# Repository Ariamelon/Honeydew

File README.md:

# Honeydew
~60% 63-key QMK-compatible unified split ergonomic keyboard.

## Disclaimer
This keyboard is licensed under CERN-OHL-S-2.0 and runs [QMK Firmware](https://qmk.fm/). The layout is based on the [Cantaloupe](https://github.com/Ariamelon/Cantaloupe) layout, but with each half rotated 15 degrees inwards.

## Key Features
* Ergonomic unsplit 60-key vertically staggered layout with thumb cluster, pinky stagger and arrow keys, plus 3 keys in the middle.
* Each half is rotated 15 degrees inwards.
* On-board Raspberry Pi RP2040 processor.
* Uses shift registers for the columns.
* SWD header for debugging purposes.
* USB-C input with full ESD protection and up to 15W of power depending on source capability.
* MX switch support with kailh hot-swap sockets.
* 40mm cirque trackpad support in the middle, alternately supports a 34mm trackball instead of the trackpad.
* Per-key RGB backlight, illuminated center ring and ARGB header for adding more.
* Rotary encoder ring around the trackball or trackpad.
* 1.5" 128x128 SSD1351 RGB QP OLED support, either bare OLED panel or using the Waveshare breakout board.
* Gasket-mount case held together with magnets.

## Changelog
* 22/10/2024: License updated to CERN-OHL-S-2.0.
* 11/06/2023: Updated BOM. Added new tentative plate file. Updated 3D files.
* 20/05/2023: Added scroll wheel rotary encoder and mouse switch for thumb scroll wheel, replacing bottom 2u key.
* 19/05/2023: Improved switch footprints. Changed 3v3 regulator to XC6206P332MR.
* 15/05/2023: Finished routing RGB LEDs.
* 05/05/2023: Changed PMOS switch to TPS2595, set to ~3A current limit. Got rid of RGB current measurement. Added enable jumper for 13V OLED PSU (only jump when in use to reduce noise when not in use). Still not done with RGB LED routing.
* 25/04/2023: Added current and voltage measurement for VBUS in and current measurement for the RGB output. Added PMOS power switch to fully turn off RGB LEDs when not in use. Rerouted the PCB. Moved OLED ribbon cable cutout and expanded it length-wise. Changed position of various components for better routing. Changed bulk capacitance of RGB LEDs to 5 x 22u capacitors. Changed the four N mosfets to two much smaller dual N mosfets. Still need to do RGB routing!
* 17/04/2023: Large update. Changed position of thumb buttons and added another button. Revamped shape of PCB again. Changed PER60 to PER56. Added 30-pin FFC receptacle for direct OLED panel mounting to the PCB (lower profile). Now using 595 shift registers for columns. Increased number of LEDs in central LED ring. Changed current limiting device to TPS2595. Connected current limiting ICs to MCU, allowing for software monitoring of current levels and changing of allowed current. Removed individual RGB capacitors and added bulk capacitance.
* 10/04/2023: Shrunk size of PCB. Added plate DXF and gerbers. Removed split comms ports and ideal diode.
* 08/04/2023: Large update. Removed single-push reset circuit, added side buttons next to the USB ports. Added pi filter to VBUS and split comms ports for more voltage filtering. Completely revamped shape of PCB for more space efficiency. Pushed each side further out and OLED further down. Added TUSB320 CC logic controller and TPS2557 current limit switch to allow the board to safely draw up to 15W (5V 3A) of power. Added mounting holes on PCB. Removed ferrite between USB shield and ground. Replaced back to back P-mosfets with ideal diode setup. Removed QMK logo (sorry). Cleaned up schematic somewhat. Added large caps to output of TPS2557. Updated STEP file and file data. Added back ground plane. Fixed rotation of production files.
* 03/04/2023: Changed level shifter to cheaper model. Slightly changed USB-C footprint. Added single-push reset circuit and removed DIP switch. Updated readme and STEP file. Moved position of USB-C ports further out.
* 02/04/2023: Changed angle of each unsplit half to 15 degrees inwards instead of 20 degrees with corresponding change to PCB and plate shape. Re-did 5V routing on the board. Added ARGB header to attach external RGB strips. Removed reverse voltage/current schottky and added back to back P-mosfets to provide the same function. Added ferrite bead to VBUS for more voltage filtering. Changed ESD protection chip to TPD4E05U06DQAR. Added USB-C expansion headers for expansion boards using split comms with the same protections as the primary USB-C input port. Added M3 earth pad for connection to a metal case. Added solder jumper to select OLED voltage as it should work fine when powered by 5V, but the option to power from 3V3 is there if required. Case to follow..
* 31/03/2023: Connected DR (data-ready) pin of TM040040 to Motion pin of PMW3360 as they serve the same function. Connected reset pins to hardware reset button instead of MCU. Added locating features to CNC case, increased wall thickness by 1mm for better magnet support (4mm now instead of 3mm) and increased size of gaskets. Redesigned trackpad mount and rotary encoder knob to allow for the illuminated ring to show up better. Added powered by QMK logo to board.
* 24/04/2023: Added level shifter to the RGB signal, just in case.
* 14/03/2023: Fixed top and bottom case STEP files. Minor fix to silk.
* 13/03/2023: V2.0 initial update. Moved switch footprint center back to normal position. Swapped capacitor and resistor at USB-C connector for ferrite bead. Moved positions of USB VBUS protection. 
* 11/03/2023: Added PH2.0 header for OLED. Changed plate to accommodate headers. Better render.
* 10/03/2023: Fixed OLED description in readme. Changed center of switches for JLC assembly.
* 09/03/2023: Shifted MCU up to reduce length of USB traces. Added holes for JLC assembly. Attempted to render a better quality image.
* 08/03/2023: Added 3D render of case, case STEP files and plate DXF and gerbers.
* 07/03/2023: Rewording of readme. Added files for JLC PCBA. Changed USB C connector and moved it away from board.
* 06/03/2023: Minor repositioning of parts.
* 05/03/2023: Added mounting holes for trackpad/trackball mount. Added CC BY 4.0 license.
* 04/03/2023: Massive mistake corrections and clarifications. Changed 22R USB resistors to 27R. Readded missing pullup for RUN pin. Changed notation of power and ground rails to the standard. Connected RGB LEDs to 5V instead of 3V3. Added keycap model to render. Changed board showcase files from SVG to PDF. Fixed error in MCU sheet. Changed flash symbol to the one used in Kicad 7.
* 03/03/2023: Initial public upload of V1.0.

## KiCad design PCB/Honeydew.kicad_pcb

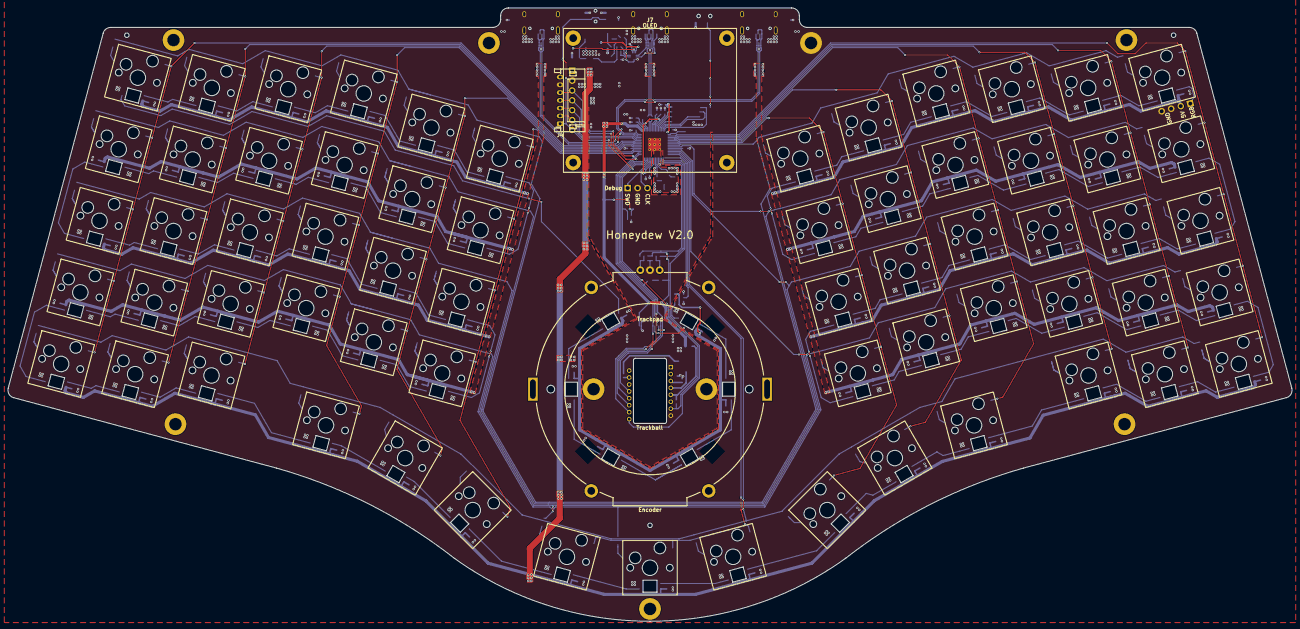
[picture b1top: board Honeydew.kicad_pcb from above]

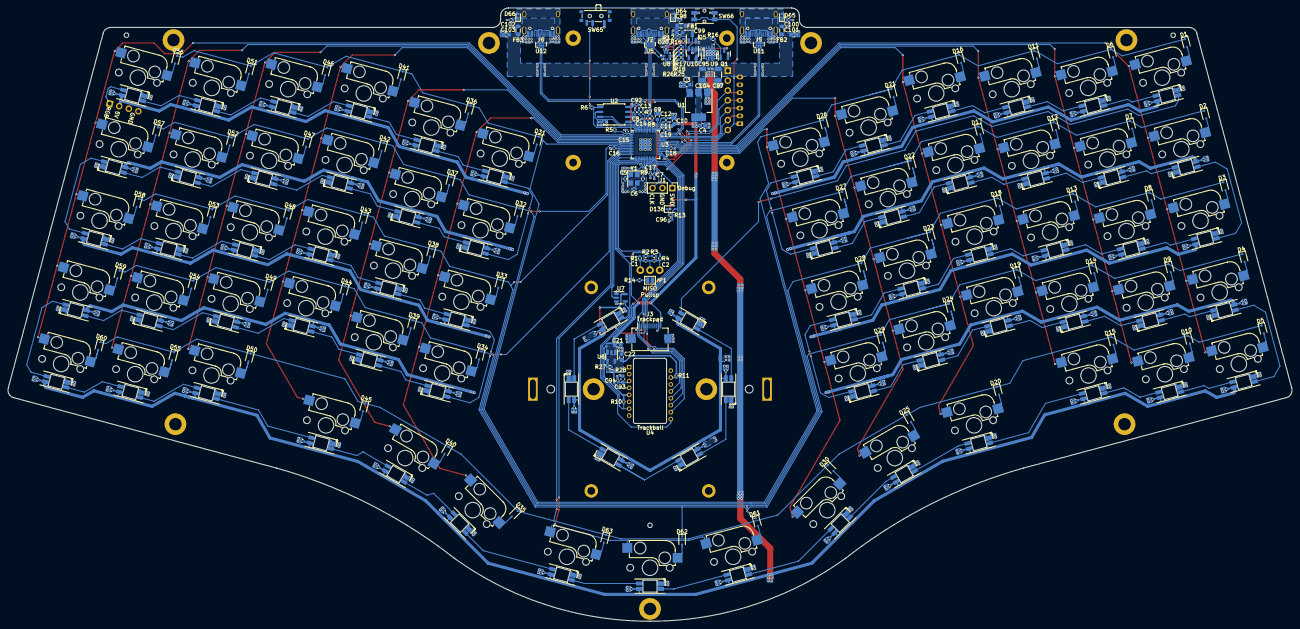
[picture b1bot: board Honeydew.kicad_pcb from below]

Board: 2 copper layers, 330.1 x 157.7 mm, 366 parts (356 on the bottom side), 206 nets.

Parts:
A1: Ariamelon Logo; Ariamelon_Logo_x3_CU
C1, C2, C98, C100, C102: 10n; C_0402_1005Metric
C3, C4, C93: 4u7; C_0603_1608Metric
C5, C6: 22p; C_0402_1005Metric
C7, C8, C11, C12, C13, C14, C15, C16, C17, C18, C19, C20, C23, C24, C25, C26, C27, C28, C29, C30, C31, C32, C33, C34, C35, C36, C37, C38, C39, C40, C41, C42, C43, C44, C45, C46, C47, C48, C49, C50, C51, C52, C53, C54, C55, C56, C57, C58, C59, C60, C61, C62, C63, C64, C65, C66, C67, C68, C69, C70, C71, C72, C73, C74, C75, C76, C77, C78, C79, C80, C81, C82, C83, C84, C85, C86, C87, C88, C89, C90, C91, C92, C94, C95, C96: 100n; C_0402_1005Metric
C9, C10, C21, C22, C99, C101, C103: 1u; C_0603_1608Metric
C97, C104: 47u; C_1206_3216Metric
D1, D2, D3, D4, D5, D6, D7, D8, D9, D10, D11, D12, D13, D14, D15, D16, D17, D18, D19, D20, D21, D22, D23, D24, D25, D26, D27, D28, D29, D30, D31, D32, D33, D34, D35, D36, D37, D38, D39, D40, D41, D42, D43, D44, D45, D46, D47, D48, D49, D50, D51, D52, D53, D54, D55, D56, D57, D58, D59, D60, D61, D62, D63, D136: 1N4148; D_SOD-323
D64, D65, D66: 5V; D_SOD-523
D67, D68, D69, D70, D71, D72, D73, D74, D75, D76, D77, D78, D79, D80, D81, D82, D83, D84, D85, D86, D87, D88, D89, D90, D91, D92, D93, D94, D95, D96, D97, D98, D99, D100, D101, D102, D103, D104, D105, D106, D107, D108, D109, D110, D111, D112, D113, D114, D115, D116, D117, D118, D119, D120, D121, D122, D123, D124, D125, D126, D127, D128, D129, D130, D131, D132, D133, D134, D135: SK6812MINI-E; YS-SK6812MINI-E
FB1, FB2, FB3: 60R@100MHz; L_0805_2012Metric
H1, H2, H3: Tooling Hole; JLC Tooling Hole
H4, H5, H6, H7, H8, H9, H10: M3; MountingHole_3.2mm_M3_Pad
J1: SWD; PinHeader_1x03_P2.54mm_Vertical
J2: USB In; HRO-TYPE-C-31-M-12
J3: Trackpad; Hirose_FH12-12S-0.5SH_1x12-1MP_P0.50mm_Horizontal
J4: OLED; JST_PH_S7B-PH-K_1x07_P2.00mm_Horizontal
J5: Split_L; HRO-TYPE-C-31-M-12
J6: Split_R; HRO-TYPE-C-31-M-12
J7: OLED; OLED_1.5_SSD1351_128x128
J9: RGB_EX; PinHeader_1x04_P2.54mm_Vertical_SIlkless
JP1: MISO_Pullup; SolderJumper-2_P1.3mm_Open_Pad1.0x1.5mm
Q1: 2N7002; SOT-23
Q5: AO3401A; SOT-23
R1, R2, R3, R4, R5, R10, R13, R14, R27: 10k; R_0402_1005Metric
R6, R9, R15: 1k; R_0402_1005Metric
R7, R8: 27; R_0402_1005Metric
R11: 39; R_0402_1005Metric
R12: 900k; R_0402_1005Metric
R16: 100k; R_0402_1005Metric
R17, R18: 270k; R_0402_1005Metric
R25: 220k; R_0402_1005Metric
R26: 82k; R_0402_1005Metric
R28: 15k; R_0402_1005Metric
SW1, SW2, SW3, SW4, SW5, SW6, SW7, SW8, SW9, SW10, SW11, SW12, SW13, SW14, SW15, SW16, SW17, SW18, SW19, SW20, SW21, SW22, SW23, SW24, SW25, SW26, SW27, SW28, SW29, SW30, SW31, SW32, SW33, SW34, SW35, SW36, SW37, SW38, SW39, SW40, SW41, SW42, SW43, SW44, SW45, SW46, SW47, SW48, SW49, SW50, SW51, SW52, SW53, SW54, SW55, SW56, SW57, SW58, SW59, SW60, SW61, SW62, SW63: CPG151101S11; MXOnly-1U-Hotswap
SW64: Encoder; PER60
SW65: Reset; SW_SPDT_PCM12
SW66: Reset; Panasonic_EVQPUL_EVQPUC
U1: AMS1117-3.3; SOT-223-3_TabPin2
U2: W25Q128JVS; SOIC-8_5.23x5.23mm_P1.27mm
U3: RP2040; QFN-56-1EP_7x7mm_P0.4mm_EP3.2x3.2mm_ThermalVias
U4: PMW3360DM-T2QU; IC_PMW3360DM-T2QU
U5, U11, U12: TPD4E05U06DQAR; USON-10_2.5x1.0mm_P0.5mm
U6: AP2127K-ADJ; SOT-23-5
U7: SN74AHCT1G125; SOT-23-5
U8: TUSB320LA; Texas_X2QFN-12_1.6x1.6mm_P0.4mm
U9: TPS2557; HVSON-8-1EP_3x3mm_P0.65mm_EP1.6x2.4mm
U10: LMV321; SOT-23-5
Y1: 12MHz; Crystal_SMD_3225-4Pin_3.2x2.5mm

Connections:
+1V1: C7.2, C8.2, C9.2, U3.23 (DVDD), U3.45 (VREG_VOUT), U3.50 (DVDD)
+2V: C22.1, R11.2, R28.1, U4.4 (VDD), U6.5 (VOUT)
+3V3: C4.2, C10.2, C11.2, C12.2, C13.2, C14.2, C15.2, C16.2, C17.2, C18.2, C19.2, C21.1, C92.2, D136.1 (K), J3.12, R2.2, R3.1, R5.1, R10.2, R13.1, R14.2, U1.2 (VO), U2.8 (VCC), U3.1 (IOVDD), U3.10 (IOVDD), U3.22 (IOVDD), U3.33 (IOVDD), U3.42 (IOVDD), U3.43 (ADC_AVDD), U3.44 (VREG_IN), U3.48 (USB_VDD), U3.49 (IOVDD), U4.5 (VDDIO), U6.1 (VIN), U6.3 (EN)
+5V: C20.2, C95.2, Q5.2 (S), R16.1, U8.12 (VDD), U9.2 (IN), U9.3 (IN), U9.4 (EN), U10.1 (+), U10.5 (V+)
+5VD: C3.2, C23.2, C24.1, C25.2, C26.2, C27.1, C28.2, C29.2, C30.1, C31.2, C32.2, C33.1, C34.2, C35.2, C36.1, C37.2, C38.2, C39.1, C40.2, C41.2, C42.1, C43.2, C44.2, C45.1, C46.2, C47.2, C48.1, C49.2, C50.2, C51.1, C52.2, C53.2, C54.1, C55.2, C56.2, C57.1, C58.2, C59.2, C60.1, C61.2, C62.2, C63.1, C64.2, C65.2, C66.1, C67.2, C68.2, C69.1, C70.2, C71.2, C72.1, C73.2, C74.2, C75.1, C76.2, C77.2, C78.1, C79.2, C80.2, C81.1, C82.2, C83.2, C84.1, C85.2, C86.2, C87.1, C88.2, C89.2, C90.1, C91.2, C97.2, C101.1, C103.1, C104.2, D67.1 (VDD), D68.1 (VDD), D69.1 (VDD), D70.1 (VDD), D71.1 (VDD), D72.1 (VDD), D73.1 (VDD), D74.1 (VDD), D75.1 (VDD), D76.1 (VDD), D77.1 (VDD), D78.1 (VDD), D79.1 (VDD), D80.1 (VDD), D81.1 (VDD), D82.1 (VDD), D83.1 (VDD), D84.1 (VDD), D85.1 (VDD), D86.1 (VDD), D87.1 (VDD), D88.1 (VDD), D89.1 (VDD), D90.1 (VDD), D91.1 (VDD), D92.1 (VDD), D93.1 (VDD), D94.1 (VDD), D95.1 (VDD), D96.1 (VDD), D97.1 (VDD), D98.1 (VDD), D99.1 (VDD), D100.1 (VDD), D101.1 (VDD), D102.1 (VDD), D103.1 (VDD), D104.1 (VDD), D105.1 (VDD), D106.1 (VDD), D107.1 (VDD), D108.1 (VDD), D109.1 (VDD), D110.1 (VDD), D111.1 (VDD), D112.1 (VDD), D113.1 (VDD), D114.1 (VDD), D115.1 (VDD), D116.1 (VDD), D117.1 (VDD), D118.1 (VDD), D119.1 (VDD), D120.1 (VDD), D121.1 (VDD), D122.1 (VDD), D123.1 (VDD), D124.1 (VDD), D125.1 (VDD), D126.1 (VDD), D127.1 (VDD), D128.1 (VDD), D129.1 (VDD), D130.1 (VDD), D131.1 (VDD), D132.1 (VDD), D133.1 (VDD), D134.1 (VDD), D135.1 (VDD), FB2.1, FB3.1, J4.7, J7.1, J9.2, U1.3 (VI), U7.5 (VCC), U9.6 (OUT), U9.7 (OUT)
/Comms - SPI/DC_OLED: J4.2, J7.6, U3.38 (GPIO26_ADC0)
/Comms - SPI/MISO: J3.2, JP1.2 (B), U3.27 (GPIO16), U4.12 (MISO)
/Comms - SPI/MOSI: J3.5, J4.5, J7.3, U3.30 (GPIO19), U4.11 (MOSI)
/Comms - SPI/MOTION: J3.4, U3.16 (GPIO13), U4.9 (MOTION)
/Comms - SPI/SCK: J3.1, J4.4, J7.4, U3.29 (GPIO18), U4.10 (SCLK)
/Comms - SPI/SS_OLED: J4.3, J7.5, U3.39 (GPIO27_ADC1)
/Comms - SPI/SS_TB: J3.3, U3.28 (GPIO17), U4.13 (NCS)
/Comms - SPI/~RST: C96.2, D136.2 (A), J4.1, J7.7, R10.1, R13.2, SW66.2 (B), U3.26 (RUN), U4.7 (NRESET)
/Comms - Split/RX: J5.A7 (D-), J5.B7 (D-), J6.A7 (D-), J6.B7 (D-), U3.40 (GPIO28_ADC2), U11.4 (IO3), U11.7 (NC), U12.4 (IO3), U12.7 (NC)
/Comms - Split/TX: J5.A6 (D+), J5.B6 (D+), J6.A6 (D+), J6.B6 (D+), U3.41 (GPIO29_ADC3), U11.2 (IO2), U11.9 (NC), U12.2 (IO2), U12.9 (NC)
/Comms - USB/CC1: J2.A5 (CC1), U5.5 (IO4), U5.6 (NC), U8.1 (CC1)
/Comms - USB/CC2: J2.B5 (CC2), U5.1 (IO1), U5.10 (NC), U8.2 (CC2)
/Comms - USB/D+: J2.A6 (D+), J2.B6 (D+), R7.1, U5.2 (IO2), U5.9 (NC)
/Comms - USB/D-: J2.A7 (D-), J2.B7 (D-), R8.1, U5.4 (IO3), U5.7 (NC)
/MCU/COL0: SW1.2 (B), SW2.2 (B), SW3.2 (B), SW4.2 (B), SW5.2 (B), U3.37 (GPIO25)
/MCU/COL1: SW6.2 (B), SW7.2 (B), SW8.2 (B), SW9.2 (B), SW10.2 (B), U3.36 (GPIO24)
/MCU/COL2: SW11.2 (B), SW12.2 (B), SW13.2 (B), SW14.2 (B), SW15.2 (B), U3.35 (GPIO23)
/MCU/COL3: SW16.2 (B), SW17.2 (B), SW18.2 (B), SW19.2 (B), SW20.2 (B), U3.34 (GPIO22)
/MCU/COL4: SW21.2 (B), SW22.2 (B), SW23.2 (B), SW24.2 (B), SW25.2 (B), U3.32 (GPIO21)
/MCU/COL5: SW26.2 (B), SW27.2 (B), SW28.2 (B), SW29.2 (B), SW30.2 (B), U3.31 (GPIO20)
/MCU/COL6: SW31.2 (B), SW32.2 (B), SW33.2 (B), SW34.2 (B), SW35.2 (B), U3.7 (GPIO5)
/MCU/COL7: SW36.2 (B), SW37.2 (B), SW38.2 (B), SW39.2 (B), SW40.2 (B), U3.6 (GPIO4)
/MCU/COL8: SW41.2 (B), SW42.2 (B), SW43.2 (B), SW44.2 (B), SW45.2 (B), U3.5 (GPIO3)
/MCU/COL9: SW46.2 (B), SW47.2 (B), SW48.2 (B), SW49.2 (B), SW50.2 (B), U3.4 (GPIO2)
/MCU/COL10: SW51.2 (B), SW52.2 (B), SW53.2 (B), SW54.2 (B), SW55.2 (B), U3.3 (GPIO1)
/MCU/COL11: SW56.2 (B), SW57.2 (B), SW58.2 (B), SW59.2 (B), SW60.2 (B), U3.2 (GPIO0)
/MCU/COLM: SW61.2 (B), SW62.2 (B), SW63.2 (B), U3.14 (GPIO11)
/MCU/RGB: D67.4 (DIN), U7.4 (Y)
/MCU/ROTA: R1.1, U3.17 (GPIO14)
/MCU/ROTB: R4.2, U3.18 (GPIO15)
/MCU/ROW0: D1.1 (K), D6.1 (K), D11.1 (K), D16.1 (K), D21.1 (K), D26.1 (K), D31.1 (K), D36.1 (K), D41.1 (K), D46.1 (K), D51.1 (K), D56.1 (K), U3.8 (GPIO6)
/MCU/ROW1: D2.1 (K), D7.1 (K), D12.1 (K), D17.1 (K), D22.1 (K), D27.1 (K), D32.1 (K), D37.1 (K), D42.1 (K), D47.1 (K), D52.1 (K), D57.1 (K), U3.9 (GPIO7)
/MCU/ROW2: D3.1 (K), D8.1 (K), D13.1 (K), D18.1 (K), D23.1 (K), D28.1 (K), D33.1 (K), D38.1 (K), D43.1 (K), D48.1 (K), D53.1 (K), D58.1 (K), D61.1 (K), U3.11 (GPIO8)
/MCU/ROW3: D4.1 (K), D9.1 (K), D14.1 (K), D19.1 (K), D24.1 (K), D29.1 (K), D34.1 (K), D39.1 (K), D44.1 (K), D49.1 (K), D54.1 (K), D59.1 (K), D62.1 (K), U3.12 (GPIO9)
/MCU/ROW4: D5.1 (K), D10.1 (K), D15.1 (K), D20.1 (K), D25.1 (K), D30.1 (K), D35.1 (K), D40.1 (K), D45.1 (K), D50.1 (K), D55.1 (K), D60.1 (K), D63.1 (K), U3.13 (GPIO10)
/PSU/~1500mA_EN: R18.2, R25.2, U8.7 (SDA/OUT1)
/PSU/~3000mA_EN: R26.2, U8.8 (SCL/OUT2)
/PSU/~EN: Q1.3 (D), U8.11 (~EN)
GND: C1.1, C2.1, C3.1, C4.1, C5.1, C6.1, C7.1, C8.1, C9.1, C10.1, C11.1, C12.1, C13.1, C14.1, C15.1, C16.1, C17.1, C18.1, C19.1, C20.1, C21.2, C22.2, C23.1, C24.2, C25.1, C26.1, C27.2, C28.1, C29.1, C30.2, C31.1, C32.1, C33.2, C34.1, C35.1, C36.2, C37.1, C38.1, C39.2, C40.1, C41.1, C42.2, C43.1, C44.1, C45.2, C46.1, C47.1, C48.2, C49.1, C50.1, C51.2, C52.1, C53.1, C54.2, C55.1, C56.1, C57.2, C58.1, C59.1, C60.2, C61.1, C62.1, C63.2, C64.1, C65.1, C66.2, C67.1, C68.1, C69.2, C70.1, C71.1, C72.2, C73.1, C74.1, C75.2, C76.1, C77.1, C78.2, C79.1, C80.1, C81.2, C82.1, C83.1, C84.2, C85.1, C86.1, C87.2, C88.1, C89.1, C90.2, C91.1, C92.1, C93.2, C94.1, C95.1, C96.1, C97.1, C98.1, C99.2, C100.1, C101.2, C102.1, C103.2, C104.1, D64.2 (A), D65.2 (A), D66.2 (A), D67.3 (VSS), D68.3 (VSS), D69.3 (VSS), D70.3 (VSS), D71.3 (VSS), D72.3 (VSS), D73.3 (VSS), D74.3 (VSS), D75.3 (VSS), D76.3 (VSS), D77.3 (VSS), D78.3 (VSS), D79.3 (VSS), D80.3 (VSS), D81.3 (VSS), D82.3 (VSS), D83.3 (VSS), D84.3 (VSS), D85.3 (VSS), D86.3 (VSS), D87.3 (VSS), D88.3 (VSS), D89.3 (VSS), D90.3 (VSS), D91.3 (VSS), D92.3 (VSS), D93.3 (VSS), D94.3 (VSS), D95.3 (VSS), D96.3 (VSS), D97.3 (VSS), D98.3 (VSS), D99.3 (VSS), D100.3 (VSS), D101.3 (VSS), D102.3 (VSS), D103.3 (VSS), D104.3 (VSS), D105.3 (VSS), D106.3 (VSS), D107.3 (VSS), D108.3 (VSS), D109.3 (VSS), D110.3 (VSS), D111.3 (VSS), D112.3 (VSS), D113.3 (VSS), D114.3 (VSS), D115.3 (VSS), D116.3 (VSS), D117.3 (VSS), D118.3 (VSS), D119.3 (VSS), D120.3 (VSS), D121.3 (VSS), D122.3 (VSS), D123.3 (VSS), D124.3 (VSS), D125.3 (VSS), D126.3 (VSS), D127.3 (VSS), D128.3 (VSS), D129.3 (VSS), D130.3 (VSS), D131.3 (VSS), D132.3 (VSS), D133.3 (VSS), D134.3 (VSS), D135.3 (VSS), H4.1, J1.2, J2.A1 (GND), J2.A12 (GND), J2.S1 (SHIELD), J3.11, J3.MP (MountPin), J4.6, J5.A1 (GND), J5.A12 (GND), J5.S1 (SHIELD), J6.A1 (GND), J6.A12 (GND), J6.S1 (SHIELD), J7.2, J9.3, J9.4, Q1.2 (S), R17.2, R27.2, SW64.C, SW65.1 (A), SW66.1 (A), U1.1 (GND), U2.4 (GND), U3.19 (TESTEN), U3.57 (GND), U4.8 (GND), U5.3 (GND), U5.8 (GND), U6.2 (GND), U7.1 (~OE), U7.3 (GND), U8.3 (PORT), U8.10 (GND), U9.1 (GND), U9.9 (GND), U10.2 (V-), U11.3 (GND), U11.8 (GND), U12.3 (GND), U12.8 (GND), Y1.2, Y1.4
unnamed: C1.2, R1.2, R2.1, SW64.A
unnamed: C2.2, R3.2, R4.1, SW64.B
unnamed: C6.2, R9.1, Y1.3
unnamed: D1.2 (A), SW1.1 (A)
unnamed: D2.2 (A), SW2.1 (A)
unnamed: D3.2 (A), SW3.1 (A)
unnamed: D4.2 (A), SW4.1 (A)
unnamed: D5.2 (A), SW5.1 (A)
unnamed: D6.2 (A), SW6.1 (A)
unnamed: D7.2 (A), SW7.1 (A)
unnamed: D8.2 (A), SW8.1 (A)
unnamed: D9.2 (A), SW9.1 (A)
unnamed: D10.2 (A), SW10.1 (A)
unnamed: D11.2 (A), SW11.1 (A)
unnamed: D12.2 (A), SW12.1 (A)
unnamed: D13.2 (A), SW13.1 (A)
unnamed: D14.2 (A), SW14.1 (A)
unnamed: D15.2 (A), SW15.1 (A)
unnamed: D16.2 (A), SW16.1 (A)
unnamed: D17.2 (A), SW17.1 (A)
unnamed: D18.2 (A), SW18.1 (A)
unnamed: D19.2 (A), SW19.1 (A)
unnamed: D20.2 (A), SW20.1 (A)
unnamed: D21.2 (A), SW21.1 (A)
unnamed: D22.2 (A), SW22.1 (A)
unnamed: D23.2 (A), SW23.1 (A)
unnamed: D24.2 (A), SW24.1 (A)
unnamed: D25.2 (A), SW25.1 (A)
unnamed: D26.2 (A), SW26.1 (A)
unnamed: D27.2 (A), SW27.1 (A)
unnamed: D28.2 (A), SW28.1 (A)
unnamed: D29.2 (A), SW29.1 (A)
unnamed: D30.2 (A), SW30.1 (A)
unnamed: D31.2 (A), SW31.1 (A)
unnamed: D32.2 (A), SW32.1 (A)
unnamed: D33.2 (A), SW33.1 (A)
unnamed: D34.2 (A), SW34.1 (A)
unnamed: D35.2 (A), SW35.1 (A)
unnamed: D36.2 (A), SW36.1 (A)
unnamed: D37.2 (A), SW37.1 (A)
unnamed: D38.2 (A), SW38.1 (A)
unnamed: D39.2 (A), SW39.1 (A)
unnamed: D40.2 (A), SW40.1 (A)
unnamed: D41.2 (A), SW41.1 (A)
unnamed: D42.2 (A), SW42.1 (A)
unnamed: D43.2 (A), SW43.1 (A)
unnamed: D44.2 (A), SW44.1 (A)
unnamed: D45.2 (A), SW45.1 (A)
unnamed: D46.2 (A), SW46.1 (A)
unnamed: D47.2 (A), SW47.1 (A)
unnamed: D48.2 (A), SW48.1 (A)
unnamed: D49.2 (A), SW49.1 (A)
unnamed: D50.2 (A), SW50.1 (A)
unnamed: D51.2 (A), SW51.1 (A)
unnamed: D52.2 (A), SW52.1 (A)
unnamed: D53.2 (A), SW53.1 (A)
unnamed: D54.2 (A), SW54.1 (A)
unnamed: D55.2 (A), SW55.1 (A)
unnamed: D56.2 (A), SW56.1 (A)
unnamed: D57.2 (A), SW57.1 (A)
unnamed: D58.2 (A), SW58.1 (A)
unnamed: D59.2 (A), SW59.1 (A)
unnamed: D60.2 (A), SW60.1 (A)
unnamed: D61.2 (A), SW61.1 (A)
unnamed: D62.2 (A), SW62.1 (A)
unnamed: D63.2 (A), SW63.1 (A)
unnamed: C98.2, D64.1 (K), FB1.2, J2.A4 (VBUS), J2.A9 (VBUS)
unnamed: C100.2, D65.1 (K), FB2.2, J5.A4 (VBUS), J5.A9 (VBUS)
unnamed: C102.2, D66.1 (K), FB3.2, J6.A4 (VBUS), J6.A9 (VBUS)
unnamed: D67.2 (DOUT), D68.4 (DIN)
unnamed: D68.2 (DOUT), D69.4 (DIN)
unnamed: D69.2 (DOUT), D70.4 (DIN)
unnamed: D70.2 (DOUT), D71.4 (DIN)
unnamed: D71.2 (DOUT), D72.4 (DIN)
unnamed: D72.2 (DOUT), D73.4 (DIN)
unnamed: D73.2 (DOUT), D78.4 (DIN)
unnamed: D74.4 (DIN), D79.2 (DOUT)
unnamed: D74.2 (DOUT), D75.4 (DIN)
unnamed: D75.2 (DOUT), D80.4 (DIN)
unnamed: D76.4 (DIN), D81.2 (DOUT)
unnamed: D76.2 (DOUT), D77.4 (DIN)
unnamed: D77.2 (DOUT), D82.4 (DIN)
unnamed: D78.2 (DOUT), D83.4 (DIN)
unnamed: D79.4 (DIN), D84.2 (DOUT)
unnamed: D80.2 (DOUT), D85.4 (DIN)
unnamed: D81.4 (DIN), D86.2 (DOUT)
unnamed: D82.2 (DOUT), D87.4 (DIN)
unnamed: D83.2 (DOUT), D88.4 (DIN)
unnamed: D84.4 (DIN), D89.2 (DOUT)
unnamed: D85.2 (DOUT), D90.4 (DIN)
unnamed: D86.4 (DIN), D91.2 (DOUT)
unnamed: D87.2 (DOUT), D92.4 (DIN)
unnamed: D88.2 (DOUT), D93.4 (DIN)
unnamed: D89.4 (DIN), D94.2 (DOUT)
unnamed: D90.2 (DOUT), D95.4 (DIN)
unnamed: D91.4 (DIN), D96.2 (DOUT)
unnamed: D92.2 (DOUT), D97.4 (DIN)
unnamed: D93.2 (DOUT), D98.4 (DIN)
unnamed: D94.4 (DIN), D99.2 (DOUT)
unnamed: D98.2 (DOUT), D99.4 (DIN)
unnamed: D95.2 (DOUT), D100.4 (DIN)
unnamed: D100.2 (DOUT), D101.4 (DIN)
unnamed: D96.4 (DIN), D101.2 (DOUT)
unnamed: D97.2 (DOUT), D102.4 (DIN)
unnamed: D102.2 (DOUT), D103.4 (DIN)
unnamed: D103.2 (DOUT), D104.4 (DIN)
unnamed: D104.2 (DOUT), D105.4 (DIN)
unnamed: D105.2 (DOUT), D110.4 (DIN)
unnamed: D106.4 (DIN), D107.2 (DOUT)
unnamed: D106.2 (DOUT), D111.4 (DIN)
unnamed: D107.4 (DIN), D112.2 (DOUT)
unnamed: D108.4 (DIN), D109.2 (DOUT)
unnamed: D108.2 (DOUT), D113.4 (DIN)
unnamed: D109.4 (DIN), D114.2 (DOUT)
unnamed: D110.2 (DOUT), D115.4 (DIN)
unnamed: D111.2 (DOUT), D116.4 (DIN)
unnamed: D112.4 (DIN), D117.2 (DOUT)
unnamed: D113.2 (DOUT), D118.4 (DIN)
unnamed: D114.4 (DIN), D119.2 (DOUT)
unnamed: D115.2 (DOUT), D120.4 (DIN)
unnamed: D116.2 (DOUT), D121.4 (DIN)
unnamed: D117.4 (DIN), D122.2 (DOUT)
unnamed: D118.2 (DOUT), D123.4 (DIN)
unnamed: D119.4 (DIN), D124.2 (DOUT)
unnamed: D120.2 (DOUT), D125.4 (DIN)
unnamed: D121.2 (DOUT), D126.4 (DIN)
unnamed: D122.4 (DIN), D127.2 (DOUT)
unnamed: D123.2 (DOUT), D128.4 (DIN)
unnamed: D124.4 (DIN), D129.2 (DOUT)
unnamed: D125.2 (DOUT), D130.4 (DIN)
unnamed: D126.2 (DOUT), D131.4 (DIN)
unnamed: D127.4 (DIN), D132.2 (DOUT)
unnamed: D128.2 (DOUT), D133.4 (DIN)
unnamed: D129.4 (DIN), D134.2 (DOUT)
unnamed: D130.2 (DOUT), D135.4 (DIN)
unnamed: D131.2 (DOUT), J9.1
unnamed: D132.4 (DIN), D133.2 (DOUT)
unnamed: D134.4 (DIN), D135.2 (DOUT)
unnamed: J1.1, U3.25 (SWD)
unnamed: J1.3, U3.24 (SWCLK)
unnamed: JP1.1 (A), R14.1
unnamed: Q1.1 (G), R16.2, U9.8 (~FAULT)
unnamed: Q5.1 (G), R15.1
unnamed: R15.2, U10.4
unnamed: R6.2, SW65.2 (B)
unnamed: U2.6 (CLK), U3.52 (QSPI_SCLK)
unnamed: U2.5 (DI(IO0)), U3.53 (QSPI_SD0)
unnamed: U2.2 (DO(IO1)), U3.55 (QSPI_SD1)
unnamed: U2.3 (IO2), U3.54 (QSPI_SD2)
unnamed: U2.7 (IO3), U3.51 (QSPI_SD3)
unnamed: R5.2, R6.1, U2.1 (~CS), U3.56 (QSPI_SS)
unnamed: U3.15 (GPIO12), U7.2 (A)
unnamed: R8.2, U3.46 (USB_DM)
unnamed: R7.2, U3.47 (USB_DP)
unnamed: C5.2, U3.20 (XIN), Y1.1
unnamed: R9.2, U3.21 (XOUT)
unnamed: R11.1, U4.15 (LED_P)
unnamed: C93.1, C94.2, U4.3 (VDDPIX)
unnamed: R27.1, R28.2, U6.4 (ADJ)
unnamed: R12.1, U8.4 (VBUS_DET)
unnamed: R17.1, R18.1, R25.1, R26.1, U9.5 (ILIM)
VBUS: C99.1, FB1.1, Q5.3 (D), R12.2, U10.3 (-)

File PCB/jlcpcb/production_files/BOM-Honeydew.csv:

Comment,Designator,Footprint,LCSC
1k,"R15,R6,R9",R_0402_1005Metric,C11702
TPS2557,U9,HVSON-8-1EP_3x3mm_P0.65mm_EP1.6x2.4mm,C130056
TUSB320LA,U8,Texas_X2QFN-12_1.6x1.6mm_P0.4mm,C132554
TPD4E05U06DQAR,"U11,U12,U5",USON-10_2.5x1.0mm_P0.5mm,C138714
AO3401A,Q5,SOT-23,C15127
10n,"C1,C100,C102,C2,C98",C_0402_1005Metric,C15195
100n,"C11,C12,C13,C14,C15,C16,C17,C18,C19,C20,C23,C24,C25,C26,C27,C28,C29,C30,C31,C32,C33,C34,C35,C36,C37,C38,C39,C40,C41,C42,C43,C44,C45,C46,C47,C48,C49,C50,C51,C52,C53,C54,C55,C56,C57,C58,C59,C60,C61,C62,C63,C64,C65,C66,C67,C68,C69,C7,C70,C71,C72,C73,C74,C75,C76,C77,C78,C79,C8,C80,C81,C82,C83,C84,C85,C86,C87,C88,C89,C90,C91,C92,C94,C95,C96",C_0402_1005Metric,C1525
22p,"C5,C6",C_0402_1005Metric,C1555
1u,"C10,C101,C103,C21,C22,C9,C99",C_0603_1608Metric,C15849
USB In,"J2,J5,J6",HRO-TYPE-C-31-M-12,C165948
4u7,"C3,C4,C93",C_0603_1608Metric,C19666
RP2040,U3,QFN-56-1EP_7x7mm_P0.4mm_EP3.2x3.2mm_ThermalVias,C2040
1N4148,"D1,D10,D11,D12,D13,D136,D14,D15,D16,D17,D18,D19,D2,D20,D21,D22,D23,D24,D25,D26,D27,D28,D29,D3,D30,D31,D32,D33,D34,D35,D36,D37,D38,D39,D4,D40,D41,D42,D43,D44,D45,D46,D47,D48,D49,D5,D50,D51,D52,D53,D54,D55,D56,D57,D58,D59,D6,D60,D61,D62,D63,D7,D8,D9",D_SOD-323,C2128
Reset,SW65,SW_SPDT_PCM12,C221841
60R@100MHz,"FB1,FB2,FB3",L_0805_2012Metric,C237300
27,"R7,R8",R_0402_1005Metric,C25100
39,R11,R_0402_1005Metric,C25164
100k,"R16,R26",R_0402_1005Metric,C25741
10k,"R1,R10,R13,R14,R2,R27,R3,R4,R5",R_0402_1005Metric,C25744
15k,R28,R_0402_1005Metric,C25756
220k,R25,R_0402_1005Metric,C25767
270k,"R17,R18",R_0402_1005Metric,C25770
900k,R12,R_0402_1005Metric,C25905
Encoder,SW64,PER60,C470483
5V,"D64,D65,D66",D_SOD-523,C502546
CPG151101S11,"SW1,SW10,SW11,SW12,SW13,SW14,SW15,SW16,SW17,SW18,SW19,SW2,SW20,SW21,SW22,SW23,SW24,SW25,SW26,SW27,SW28,SW29,SW3,SW30,SW31,SW32,SW33,SW34,SW35,SW36,SW37,SW38,SW39,SW4,SW40,SW41,SW42,SW43,SW44,SW45,SW46,SW47,SW48,SW49,SW5,SW50,SW51,SW52,SW53,SW54,SW55,SW56,SW57,SW58,SW59,SW6,SW60,SW61,SW62,SW63,SW7,SW8,SW9",MXOnly-1U-Hotswap,C5184526
SK6812MINI-E,"D100,D101,D102,D103,D104,D105,D106,D107,D108,D109,D110,D111,D112,D113,D114,D115,D116,D117,D118,D119,D120,D121,D122,D123,D124,D125,D126,D127,D128,D129,D130,D131,D132,D133,D134,D135,D67,D68,D69,D70,D71,D72,D73,D74,D75,D76,D77,D78,D79,D80,D81,D82,D83,D84,D85,D86,D87,D88,D89,D90,D91,D92,D93,D94,D95,D96,D97,D98,D99",YS-SK6812MINI-E,C524051
AMS1117-3.3,U1,SOT-223-3_TabPin2,C6186
SN74AHCT1G125,U7,SOT-23-5,C7484
Reset,SW66,Panasonic_EVQPUL_EVQPUC,C79174
LMV321,U10,SOT-23-5,C7972
2N7002,Q1,SOT-23,C8545
Trackpad,J3,Hirose_FH12-12S-0.5SH_1x12-1MP_P0.50mm_Horizontal,C88360
12MHz,Y1,Crystal_SMD_3225-4Pin_3.2x2.5mm,C9002
47u,"C104,C97",C_1206_3216Metric,C96123
AP2127K-ADJ,U6,SOT-23-5,C96343
W25Q128JVS,U2,SOIC-8_5.23x5.23mm_P1.27mm,C97521
OLED,J4,JST_PH_S7B-PH-K_1x07_P2.00mm_Horizontal,
OLED,J7,OLED_1.5_SSD1351_128x128,

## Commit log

2023-03-03 V1.0 initial update.
2023-03-03 More visible images.
2023-03-04 Changed RGB LED voltage to 5V.
2023-03-04 Massive mistake corrections and clarifications.
2023-03-04 Fixed error in MCU sheet. Changed flash symbol to the one used in Kicad 7.
2023-03-05 Added mounting holes for trackpad/trackball mount.
2023-03-06 Minor repositioning of parts.
2023-03-08 Rewording of readme. Added files for JLC PCBA. Changed USB C connector and moved it away from board.
2023-03-08 Added plate DXF and gerbers and case STEP files.
2023-03-09 Shifted MCU up to reduce length of USB traces. Added holes for JLC assembly.
2023-03-09 Updated board image files
2023-03-10 Fixed OLED description.
2023-03-10 Changed center of switches for JLC assembly.
2023-03-11 Added PH2.0 header for OLED. Changed plate to accommodate headers.
2023-03-11 Better render.
2023-03-13 V1.1 update.
2023-03-14 Fixed top and bottom case STEP files.
2023-03-15 Minor fix to silk.
2023-03-24 Added level shifter to the RGB signal, just in case.
2023-03-25 Changed knob and trackpad mount STEP files
2023-03-31 More V1.1 updates
2023-03-31 Image added. Keyboard tested and is working other than the QP display.
2023-04-02 Initial V2.0 update.
2023-04-03 Additional changes.
2023-04-03 Updated readme and step file.
2023-04-03 Moved position of USB-C ports further out.
2023-04-08 Large update.
2023-04-08 Added large caps to output of TPS2557. Updated STEP file and file data.
2023-04-08 Added back ground plane. Fixed rotation of production files.
2023-04-10 Shrunk size of PCB.
2023-04-10 Added plate DXF and gerbers. Removed split comms ports and ideal diode.
2023-04-17 17/04/2023 large update.
2023-04-19 Rerouting.
2023-04-25 3/4-done update.
    Added current and voltage measurement for VBUS in and current measurement for the RGB output. Added PMOS power switch to fully turn off RGB LEDs when not in use. Rerouted the PCB. Moved OLED ribbon c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
2023-05-05 05/05/2023 update.
2023-05-05 BLE version incomplete update.
2023-05-15 Finished routing RGB LEDs.
2023-05-19 Improved switch footprints and changed LDO.
2023-05-20 Added thumb wheel encoder in 2u slot.
2023-06-11 Updated BOM. Added new tentative plate file.
2023-06-11 Updated 3D files.
2023-06-24 Update in progress (will be squashed)
2023-06-27 Initial V2.1 update.
2023-06-30 Routed 13V EN pin to the MCU. Removed solder jumper.
2023-07-10 In progress update
2023-07-14 14/07/2023 update
    Replaced 1N4148 switch diodes with BAV70. Replaced switch footprints with combination MX/Choc hotswap footprints. Replaced flash IC with much smaller version. Removed buttons and USB-C port and repla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
2023-07-14 Added footprint for PTS645 SMT and THT parts to the mouse switch in the thumb encoder.
2023-07-16 16/07/2023 update
    Updated case file. Added individual case files. Added kicad plate files.
2023-07-17 17/07/2023 update
    Changed 20 pin FFC connector to 14 pin JST SH connector. Repositioned components.
2023-07-18 18/07/2023 update.
    Changed JST connector back to 20 pin FFC. Centered connector. Increased size of PMW3360 cutout.
2023-07-21 21/07/2023 update.
    Fixed routing. Changed 20 pin FFC to 7 pin and 8 pin JST SH connector.
2023-07-26 25/07/2023 update
    Changed 8 pin JST SH connector to 6 pin. Pushed JST connectors back. Improved 3D model of SSD1351. Minor fix to PER56 footprint.
2023-07-26 26/07/2023 update
    Sent to JLC (V3.0 release version). Slightly increased size of screw hole pads. Added two more screw holes. Added mounting holes to plate. Flipped gerbers for scrollwheel plate.
2023-07-29 28/07/2023 update
    Removed center ring encoder, cirque trackpad and PMW3360 support. Added VIK header and hole in the center of the PCB for the Kiwano. Changed JST connectors back to 20 pin FFC. Total rearrangement of 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
2023-07-30 30/07/2023 update
    Added VIK keyboard certification card. Added USB connector back to PCB, but left the two buttons on a separate daughterboard. Modified case to accommodate large VIK module.
2023-07-30 Updated production files.
2023-07-31 31/07/2023 update
    Removed button daughterboard. Reduced size of case and gaskets and added locating features. Added o-ring mounting for the PCB to the bottom case. Added fittings BOM.
2023-08-01 01/08/2023 update
    Removed 3D files for trackpad mount and knob, moved to Kiwano repository. Increased size of center hole in plate. Increased size of center hole in plate. Added renders with trackball configurations (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
2023-08-05 04/08/2023 update
    Updated SK6812 MINI-E and switch footprints. Changed VIK FFC to FH12. Fixed VIK footprint. Replaced second TPS2595 with AO3401 PFET. Fixed trackpad mount, thumb scroll wheel and scroll wheel mount.
2023-08-05 08/05/2023 update
    Fixed switch and SK6812 MINI-E footprints to get rid of DRC errors. Fixed EC10 footprint and merged together PTS645 and D2F footprints. Fixed plate files to fit JLC 1.6mm minimum slot specification. 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
2023-08-07 06/08/2023 update
    Changed switch footprint back to MX only, as it's too much money to risk on an experimental footprint, and rerouted the relevant traces. Cleaned up footprint library by removing many unused footprint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
2023-08-08 08/08/2023 update
    Fixed case render.
2023-08-16 16/08/2023 update
    Updated to V3.1. Fixed VIK wiring (RGB and SDA were swapped). Added another BAV70 for the bottom button in the thumb cluster. Added DNP attribute to R15. Added jumper for VIK 5V rail.
2023-08-17 17/08/2023 update
    Moved gasket mounts from plate to PCB. Changed USB C connector. Modified case to accommodate. Tweaked thumb scroll holder.
2023-08-27 27/08/2023 update
    Added unified library for all symbols, footprints and 3D files. Changed MCU to STM32F072RBT6. Removed OLED, voltage and current sensing, USB CC circuitry and shift registers. Changed ESD protection c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
2023-08-28 28/08/2023 update
    Added test points for VIK connector. Refined case and scrollwheel design. Added pull-up resistor to RGB trace. Added Acheron single-push reset circuit. Updated STEP files.
2023-08-29 29/08/2023 update
    Reassigned I2C pins due to DMA issues and rerouted board. Added test point for BOOT0. Added additional ground vias.
2023-09-02 02/09/2023 update
    Added ribs to bottom case for less warping, deformation and shrinkage risk. Updated library.
2023-09-18 18/09/2023 update
    Fixed .gitignore file. Updated library.
2023-09-27 27/09/2023 update
    Added image. Small change to scrollwheel 3D file for smoother scrolling.
2023-10-04 29/09/2023 update
    Added PCBWay sponsorship disclaimer to the readme. Updated library.
2024-10-22 License updated to CERN-OHL-S-2.0.

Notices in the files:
PCB/Honeydew.kicad_pcb:
Licensed under CC BY 4.0.
